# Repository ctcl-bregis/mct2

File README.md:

<div>
  
</div>

# MediaCow Touch 2
MediaCow Touch 2 "Paris" is the successor to MediaCow Touch (1) "Nashville" which is a DIY portable tablet computer.

This repository has all of the hardware designs and some software for the project.

See [MediaCow Touch 2 page](https://ctcl.lgbt/projects/mct2/) for more information.

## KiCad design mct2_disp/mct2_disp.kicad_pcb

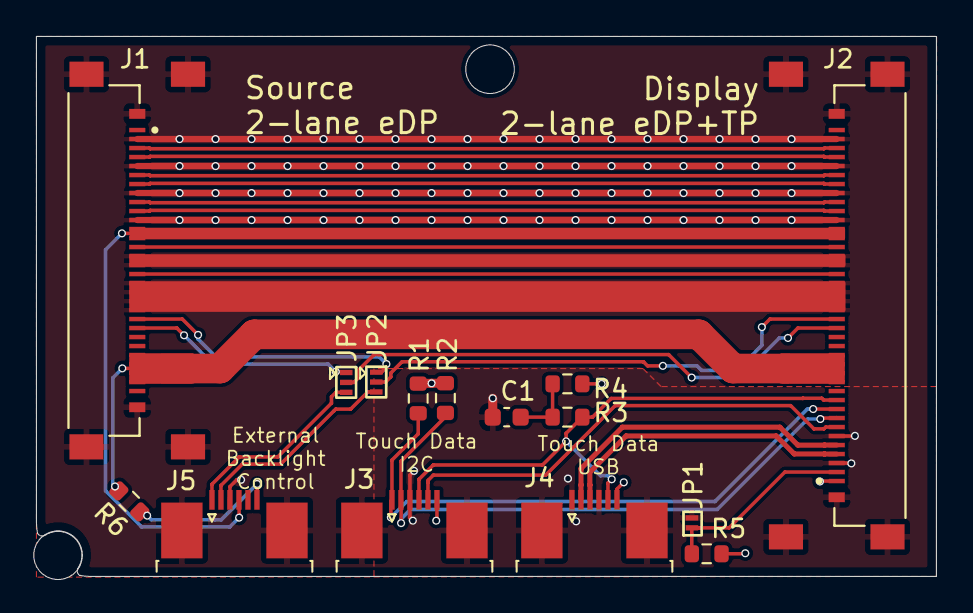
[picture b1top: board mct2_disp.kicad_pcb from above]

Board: 4 copper layers, 50.0 x 30.0 mm, 17 parts (0 on the bottom side), 27 nets.

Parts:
C1: 4.7uF; C_0603_1608Metric
H1, H2: MountingHole; MountingHole_2.7mm_M2.5
J1: 20455-030E-76; IPEX_20455-030E-76
J2: 20455-040E-76; IPEX_20455-040E-76
J3: Touch Data - I2C; TE_0-1734839-6_1x06-1MP_P0.5mm_Horizontal
J4: Touch Data - USB; TE_0-1734839-6_1x06-1MP_P0.5mm_Horizontal
J5: External Backlight Control; TE_0-1734839-6_1x06-1MP_P0.5mm_Horizontal
JP1: Jumper_2_Open; SolderJumper-2_P1.3mm_Open_Pad1.0x1.5mm
JP2, JP3: Jumper_3_Open; SolderJumper-3_P1.3mm_Open_Pad0.3x0.7mm
R1, R2: 2.2K; R_0603_1608Metric
R3: 1K; R_0603_1608Metric
R4, R5: 10K; R_0603_1608Metric
R6: 0R; R_0603_1608Metric

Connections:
BL_EN: J2.19, JP2.2 (C)
BL_EN_EXT: J5.2, JP2.3 (B)
BL_EN_MU: J1.22, JP2.1 (A)
BL_PWM: J2.18, JP3.2 (C)
BL_PWM_EXT: J5.1, JP3.3 (B)
BL_PWM_MU: J1.23, JP3.1 (A)
BL_PWR: J1.26, J1.27, J1.28, J1.29, J2.12, J2.13, J2.14, J2.15, R6.2
EDP_AUX_N: J1.10, J2.31
EDP_AUX_P: J1.9, J2.32
EDP_HPD: J1.17, J2.24
EDP_TX0_N: J1.6, J2.35
EDP_TX0_P: J1.7, J2.34
EDP_TX1_N: J1.3, J2.38
EDP_TX1_P: J1.4, J2.37
GND: C1.2, J1.2, J1.5, J1.8, J1.11, J1.15, J1.16, J1.18, J1.19, J1.20, J1.21, J1.S1 (SHIELD), J1.S2 (SHIELD), J1.S3 (SHIELD), J1.S4 (SHIELD), J2.3, J2.6, J2.20, J2.21, J2.22, J2.23, J2.25, J2.26, J2.30, J2.33, J2.36, J2.39, J2.S1 (SHIELD), J2.S2 (SHIELD), J2.S3 (SHIELD), J2.S4 (SHIELD), J3.3, J3.MP (MountPin), J4.1, J4.4, J4.MP (MountPin), J5.3, J5.MP (MountPin), JP1.2 (B)
LCD_BIST: J1.14, J2.27
LCD_VCC: J1.12, J1.13, J2.28, J2.29, J5.4
unnamed: C1.1, R3.2, R4.2
unnamed: J5.6, R6.1
TP_I2C_SCL: J2.9, J3.1, R1.2
TP_I2C_SDA: J2.8, J3.2, R2.2
TP_INT: J2.7, J3.5
TP_RS: J2.2, JP1.1 (A), R5.2
TP_RST: J2.10, J3.4, J4.5, R3.1
TP_USB_N: J2.4, J4.3
TP_USB_P: J2.5, J4.2
TP_VCC: J2.1, J3.6, J4.6, R1.1, R2.1, R4.1, R5.1

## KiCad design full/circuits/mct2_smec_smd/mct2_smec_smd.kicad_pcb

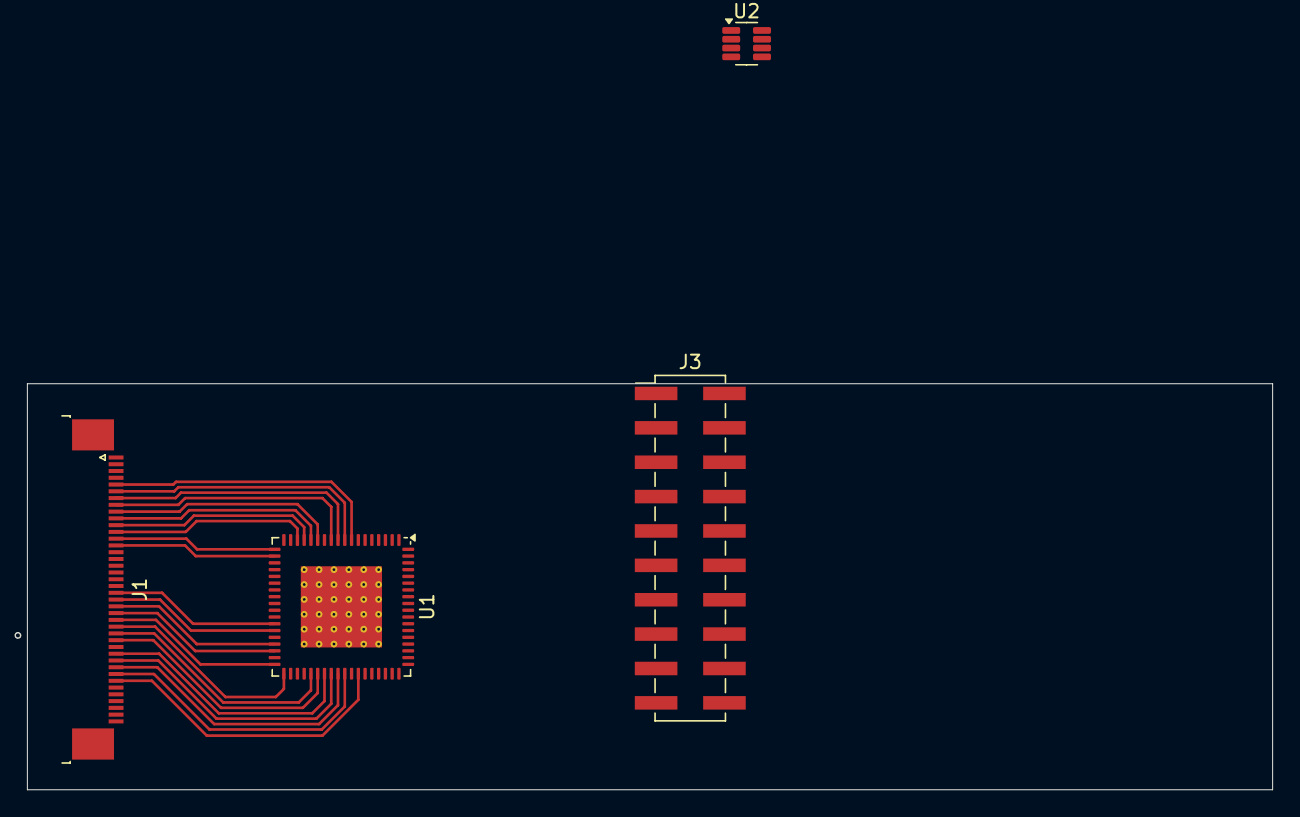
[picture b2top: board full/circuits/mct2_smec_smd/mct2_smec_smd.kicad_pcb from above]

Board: 4 copper layers, 92.0 x 30.0 mm, 4 parts (0 on the bottom side), 28 nets.

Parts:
J1: Input 1x40 FPC; TE_4-1734839-0_1x40-1MP_P0.5mm_Horizontal
J3: Conn_02x15_Odd_Even; PinHeader_2x10_P2.54mm_Vertical_SMD
U1: LIFCL-17-7SG72C; QFN-72-1EP_10x10mm_P0.5mm_EP6x6mm_ThermalVias
U2: SOT-23-8

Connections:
GND: J1.3, J1.29, J1.36, J3.1, J3.2, J3.6, J3.7, J3.10, J3.13, J3.16, J3.19, J3.20
MIPI_CLK_N: J3.3, U1.3 (DPHY0_DN0)
MIPI_CLK_P: J3.5, U1.4 (DPHY0_DP0)
MIPI_D0_N: J3.15, U1.69 (DPHY0_CKN)
MIPI_D0_P: J3.17, U1.68 (DPHY0_CKP)
RGB_B0: J1.21, U1.30 (PB66A)
RGB_B1: J1.22, U1.31 (PB66B)
RGB_B2: J1.23, U1.33 (PB68A)
RGB_B3: J1.24, U1.34 (PB68B)
RGB_B4: J1.25, U1.36 (PB70A)
RGB_B5: J1.26, U1.37 (PB70B)
RGB_B6: J1.27, U1.41 (PR9A)
RGB_B7: J1.28, U1.42 (PR7A)
RGB_DE: J1.34, U1.48 (PR3B)
RGB_EN: J1.31, U1.44 (PR7B)
RGB_G0: J1.13, U1.19 (PB26A)
RGB_G1: J1.14, U1.20 (PB26B)
RGB_HSYNC: J1.32, U1.45 (PR5B)
RGB_PCLK: J1.30, U1.43 (PR9B)
RGB_R0: J1.5, U1.8 (PB30B)
RGB_R1: J1.6, U1.9 (PB30A)
RGB_R2: J1.7, U1.10 (PB20B)
RGB_R3: J1.8, U1.11 (PB20A)
RGB_R4: J1.9, U1.13 (PB16B)
RGB_R5: J1.10, U1.14 (PB16A)
RGB_R6: J1.11, U1.15 (PB18B)
RGB_R7: J1.12, U1.16 (PB18A)
RGB_VSYNC: J1.33, U1.46 (PR5A)

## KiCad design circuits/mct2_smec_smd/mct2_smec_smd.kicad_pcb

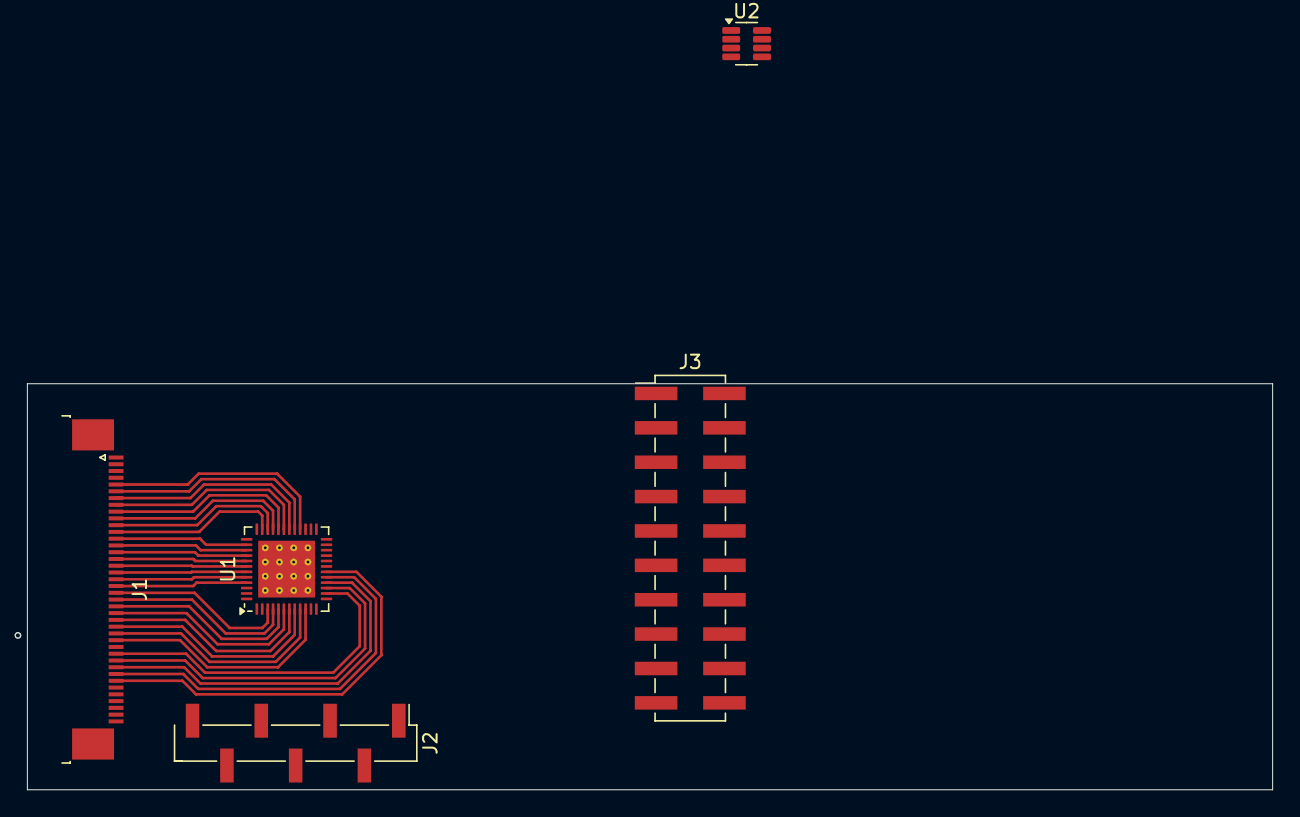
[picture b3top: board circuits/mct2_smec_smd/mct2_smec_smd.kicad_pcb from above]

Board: 4 copper layers, 92.0 x 30.0 mm, 5 parts (0 on the bottom side), 37 nets.

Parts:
J1: Input 1x40 FPC; TE_4-1734839-0_1x40-1MP_P0.5mm_Horizontal
J2: Conn_01x07; PinHeader_1x07_P2.54mm_Vertical_SMD_Pin1Left
J3: Conn_02x15_Odd_Even; PinHeader_2x10_P2.54mm_Vertical_SMD
U1: GW1N-UV2QN48C7/I6; QFN-48-1EP_6x6mm_P0.4mm_EP4.2x4.2mm_ThermalVias
U2: SOT-23-8

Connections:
GND: J1.3, J1.29, J1.36, J3.1, J3.2, J3.6, J3.7, J3.10, J3.13, J3.16, J3.19, J3.20, U1.2 (VSS), U1.26 (VSS)
JTAG_MODE0: J2.6, U1.13 (IOT2A/MODE0)
JTAG_RECONFIG_N: J2.7, U1.48 (IOT16B/RECONFIG_N)
JTAG_TDO: J2.5, U1.11 (IOT7A/TDO)
MIPI_CLK_N: J3.3, U1.23 (IOL15A)
MIPI_CLK_P: J3.5, U1.22 (IOL15B)
MIPI_D0_N: J3.15, U1.21 (IOL11B)
MIPI_D0_P: J3.17, U1.20 (IOL11A)
RGB_B0: J1.21, U1.3 (IOT16A/JTAGSEL_N)
RGB_B1: J1.22, U1.4 (IOT14B/GCLKC_1/SDA)
RGB_B2: J1.23, U1.5 (IOT14A/GCLKT_1/SCL)
RGB_B3: J1.24, U1.6 (IOT11A/GCLKT_0)
RGB_B4: J1.25, U1.7 (IOT11B/GCLKC_0)
RGB_B5: J1.26, U1.8 (IOT9B/TMS)
RGB_B6: J1.27, U1.9 (IOT9A/TCK)
RGB_B7: J1.28, U1.10 (IOT7B/TDI)
RGB_DE: J1.34, U1.18 (IOL6A/GCLKT_7)
RGB_EN: J1.31, U1.15 (IOL4A/LPLL_T_fb)
RGB_G0: J1.13, U1.38 (IOR13A)
RGB_G1: J1.14, U1.39 (IOR13B)
RGB_G2: J1.15, U1.40 (IOR11B/GCLKC_2)
RGB_G3: J1.16, U1.41 (IOR11A/GCLKT_2)
RGB_G4: J1.17, U1.42 (IOR5B/MO/D6)
RGB_G5: J1.18, U1.43 (IOR5A/MI/D7)
RGB_G6: J1.19, U1.44 (IOR3B/D3)
RGB_G7: J1.20, U1.45 (IOR3A/D2)
RGB_HSYNC: J1.32, U1.16 (IOL5A/LPLL_T_in)
RGB_PCLK: J1.30, U1.14 (IOL4B/LPLL_C_fb)
RGB_R0: J1.5, U1.28 (IOB5B/SO)
RGB_R1: J1.6, U1.29 (IOB5A/SCLK)
RGB_R2: J1.7, U1.30 (IOB7B/GCLKC_4)
RGB_R3: J1.8, U1.31 (IOB7A/GCLKT_4)
RGB_R4: J1.9, U1.32 (IOB13B)
RGB_R5: J1.10, U1.33 (IOB13A)
RGB_R6: J1.11, U1.34 (IOB18A/SSPI_CS_N)
RGB_R7: J1.12, U1.35 (IOB18B/SI)
RGB_VSYNC: J1.33, U1.17 (IOL5B/LPLL_C_in)

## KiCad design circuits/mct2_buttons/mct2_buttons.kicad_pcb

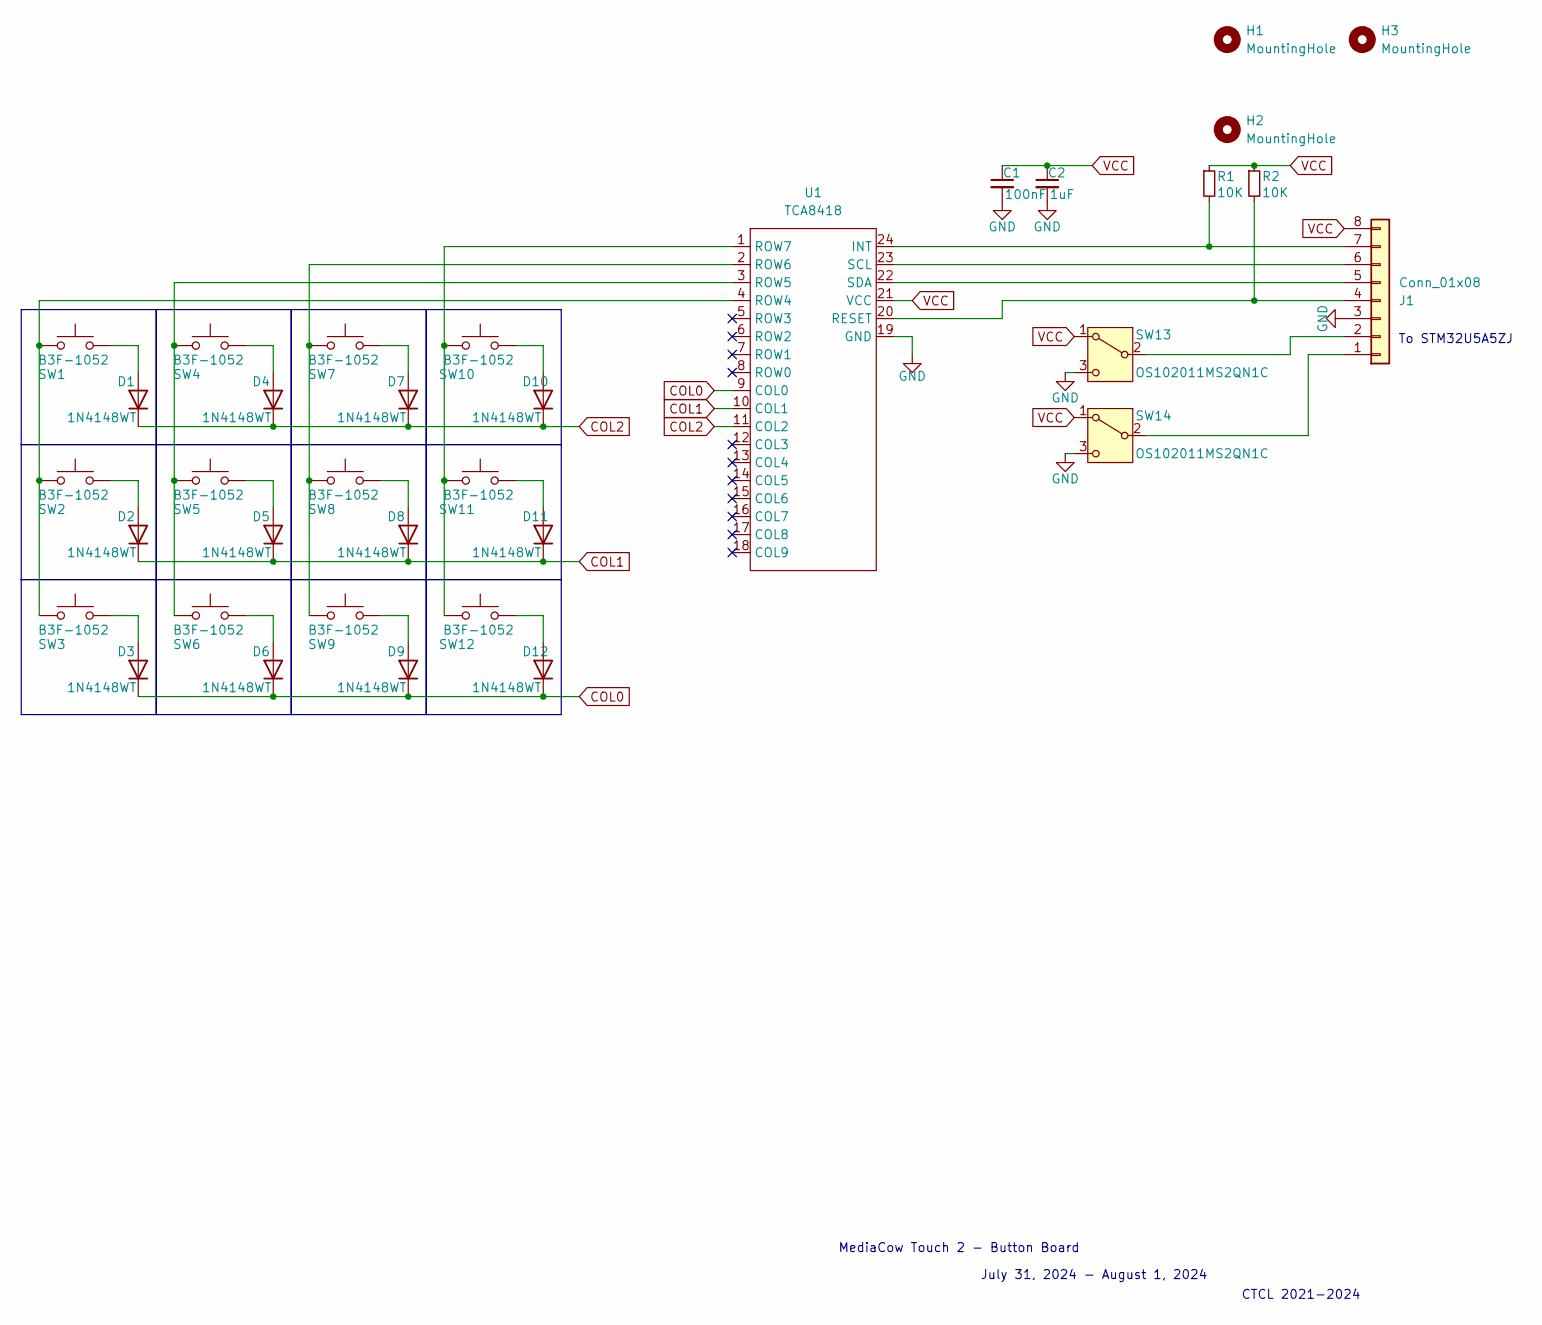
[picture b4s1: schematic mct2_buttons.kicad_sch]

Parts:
C1: 100nF; C_0603_1608Metric
C2: 1uF; C_0603_1608Metric
D1, D2, D3, D4, D5, D6, D7, D8, D9, D10, D11, D12: 1N4148WT; D_SOD-523
H1, H2, H3: MountingHole; MountingHole_2.2mm_M2_Pad
J1: Conn_01x08; Molex_200528-0080_1x08-1MP_P1.00mm_Horizontal
R1, R2: 10K; R_0603_1608Metric
SW1, SW2, SW3, SW4, SW5, SW6, SW7, SW8, SW9, SW10, SW11, SW12: B3F-1052; SW_TH_Tactile_Omron_B3F-10xx_center
SW13, SW14: OS102011MS2QN1C; SW_Slide_SPDT_Straight_CK_OS102011MS2Q_center
U1: TCA8418; Texas_RTW_WQFN-24-1EP_4x4mm_P0.5mm_EP2.7x2.7mm

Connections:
COL0: D3.1 (K), D6.1 (K), D9.1 (K), D12.1 (K), U1.9 (COL0)
COL1: D2.1 (K), D5.1 (K), D8.1 (K), D11.1 (K), U1.10 (COL1)
COL2: D1.1 (K), D4.1 (K), D7.1 (K), D10.1 (K), U1.11 (COL2)
GND: C1.2, C2.2, J1.3, SW13.3 (C), SW14.3 (C), U1.19 (GND)
unnamed: D1.2 (A), SW1.2
unnamed: D2.2 (A), SW2.2
unnamed: D3.2 (A), SW3.2
unnamed: D4.2 (A), SW4.2
unnamed: D5.2 (A), SW5.2
unnamed: D6.2 (A), SW6.2
unnamed: D7.2 (A), SW7.2
unnamed: D8.2 (A), SW8.2
unnamed: D9.2 (A), SW9.2
unnamed: D10.2 (A), SW10.2
unnamed: D11.2 (A), SW11.2
unnamed: D12.2 (A), SW12.2
unnamed: J1.1, SW14.2 (B)
unnamed: J1.2, SW13.2 (B)
unnamed: J1.4, R2.2, U1.20 (RESET)
unnamed: J1.5, U1.22 (SDA)
unnamed: J1.6, U1.23 (SCL)
unnamed: J1.7, R1.2, U1.24 (INT)
unnamed: SW1.1, SW2.1, SW3.1, U1.4 (ROW4)
unnamed: SW4.1, SW5.1, SW6.1, U1.3 (ROW5)
unnamed: SW7.1, SW8.1, SW9.1, U1.2 (ROW6)
unnamed: SW10.1, SW11.1, SW12.1, U1.1 (ROW7)
VCC: C1.1, C2.1, J1.8, R1.1, R2.1, SW13.1 (A), SW14.1 (A), U1.21 (VCC)

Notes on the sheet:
July 31, 2024 - August 1, 2024
CTCL 2021-2024
To STM32U5A5ZJ
MediaCow Touch 2 - Button Board

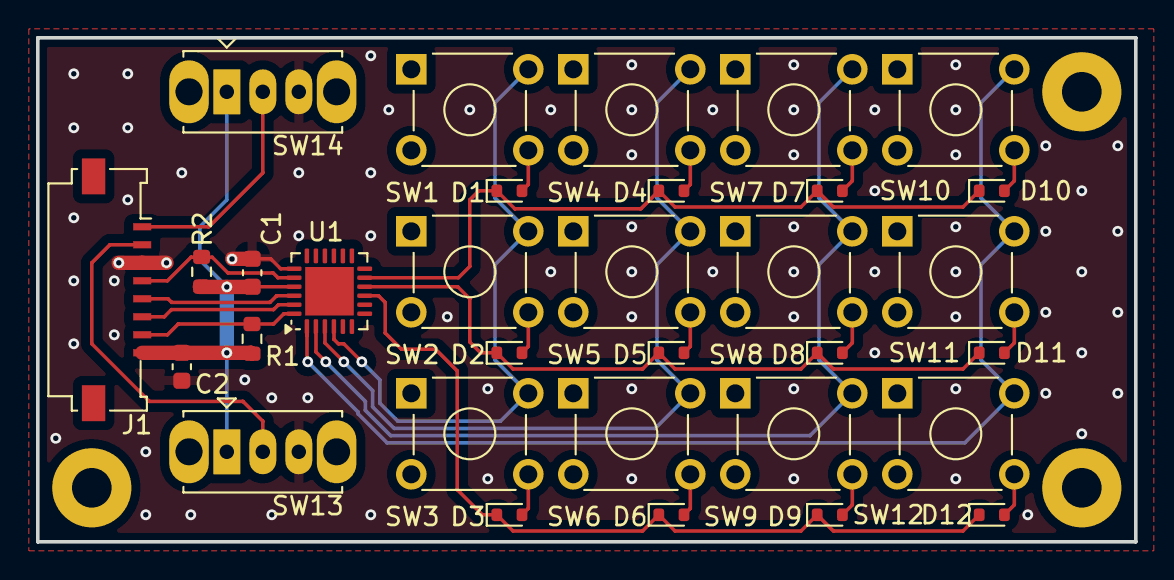
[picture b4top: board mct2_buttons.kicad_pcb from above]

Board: 2 copper layers, 61.0 x 28.0 mm, 35 parts (0 on the bottom side), 27 nets.

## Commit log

2024-07-07 July 7 2024
2024-07-07 splash update
2024-07-09 readme and physical diagram update
2024-07-11 block diagram and schematic update
2024-07-12 figuring out USB3
2024-07-14 July 13, 2024
2024-07-14 block diagram updates
2024-07-15 hw block diagram update July 15 2024
2024-07-19 diagram updates, case update
2024-07-19 schem update July 19 2024
2024-07-21 July 21, 2024
2024-07-23 July 23, 2024
2024-07-25 Schematic updates July 25, 2024
2024-07-25 schem update 2 July 25, 2024
2024-07-28 July 27, 2024
2024-08-01 Aug 1, 2024
2024-08-02 Aug 2, 2024
2024-08-03 Aug 3, 2024
2024-08-07 Aug 7, 2024 stuff in case I don't work on this before going to FMB
2024-08-11 Aug 10, 2024
2024-08-11 Aug 11, 2024 1
2024-08-11 Aug 11, 2024 2
2024-08-13 Aug 13, 2024
2024-08-16 Aug 14, 2024 old stuff
2024-08-17 Aug 17, 2024
2024-08-18 Aug 17, 2024 2
2024-08-19 Aug 19, 2024
2024-08-21 Aug 21, 2024 1
2024-08-22 Aug 22, 2024 1
2024-08-26 Aug 26, 2024
2024-08-28 Aug 28, 2024
2024-08-29 Aug 29, 2024 1
2024-08-29 Aug 29, 2024 2
2024-08-31 Aug 31, 2024
2024-09-03 Sep 3, 2024 1
2024-09-04 Sep 4, 2024 1
2024-09-04 Sep 4, 2024 2
2024-09-05 Sep 5, 2024 1
2024-09-05 Sep 5, 2024 2
2024-09-12 Sep 12, 2024 2
2024-09-17 Sep 17, 2024 1
2024-09-26 Sep 26, 2024 1
2024-10-03 Oct 3, 2024, probably nothing of note
2024-10-15 nothing, Oct 14, 2024
2024-11-29 begin refactoring
2024-12-01 Dec 1, 2024 video switch PCB idea
2024-12-08 20241208 1
2024-12-10 20241209-1 8K backgrounds
2024-12-14 20241214-1
2024-12-16 20241216-1
2024-12-23 20241223-1 More backgrounds
2024-12-23 20241223-2 markdown formatting
2024-12-24 20241224-1 fix resolution for mct2_rockwood_1.png
2025-01-08 20250107-1 Type-C controller ideas and more backgrounds
2025-01-27 20250127-1 case designs
2025-01-30 20250129-1
2025-01-30 20250129-2
2025-02-16 20250216-1
2025-02-20 20250220-1 Add GOWIN FPGA symbol
2025-02-24 20250224-1
2025-02-24 20250224-2
2025-03-06 20250306-1
2025-03-06 20250306-2
2025-03-11 20250311-1
2025-03-13 20250313-1
2025-03-16 20250316-1
2025-03-24 20250324-1
2025-04-10 20250410-1
2025-04-10 20250410-2
2025-04-10 20250410-3
2025-04-15 20250414-1
2025-04-15 20250415-1
2025-04-23 20250423-1
2025-04-25 20250425-1
2025-04-25 20250425-2
2025-04-26 20250426-1 Remove current codename
2025-05-04 20250504-1
2025-05-10 20250509-1
2025-05-24 20250524-1
2025-05-29 20250529-1
2025-06-04 20250604-1
2025-06-10 20250610-1
2025-06-28 20250628-1
2025-07-12 20250712-1 mv docs from website to repo
